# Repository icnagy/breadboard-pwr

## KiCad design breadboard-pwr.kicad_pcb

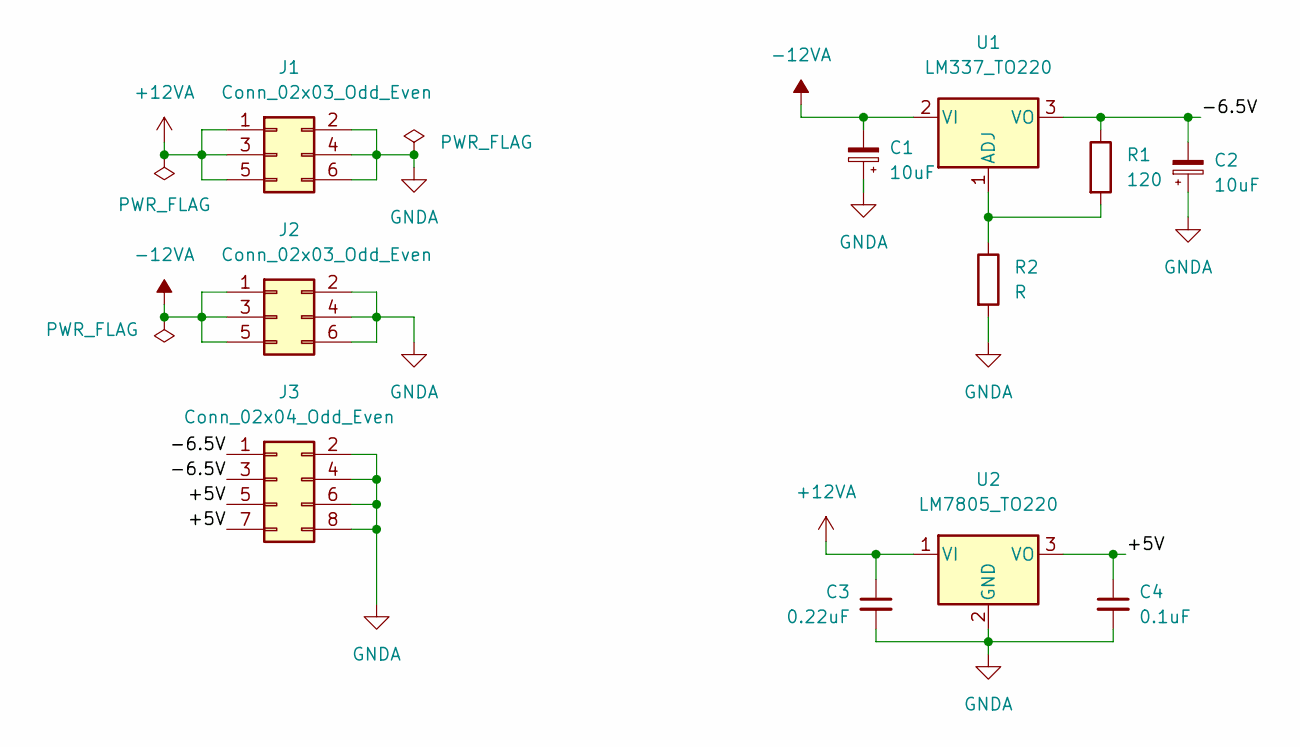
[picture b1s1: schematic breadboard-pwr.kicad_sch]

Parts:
C1, C2: 10uF; CP_Radial_D5.0mm_P2.00mm
C3: 0.22uF; C_Disc_D4.7mm_W2.5mm_P5.00mm
C4: 0.1uF; C_Disc_D4.7mm_W2.5mm_P5.00mm
J1, J2: Conn_02x03_Odd_Even; PinHeader_2x03_P2.54mm_Vertical
J3: Conn_02x04_Odd_Even; PinHeader_2x04_P2.54mm_Vertical
R1: 120; R_Axial_DIN0204_L3.6mm_D1.6mm_P2.54mm_Vertical
R2: R; R_Axial_DIN0204_L3.6mm_D1.6mm_P2.54mm_Vertical
U1: LM337_TO220; TO-220-3_Vertical
U2: LM7805_TO220; TO-220-3_Vertical

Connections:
+12VA: C3.1, J1.1, J1.3, J1.5, U2.1 (VI)
-12VA: C1.2, J2.1, J2.3, J2.5, U1.2 (VI)
/+5V: C4.1, J3.5, J3.7, U2.3 (VO)
/-6.5V: C2.2, J3.1, J3.3, R1.1, U1.3 (VO)
GNDA: C1.1, C2.1, C3.2, C4.2, J1.2, J1.4, J1.6, J2.2, J2.4, J2.6, J3.2, J3.4, J3.6, J3.8, R2.2, U2.2 (GND)
unnamed: R1.2, R2.1, U1.1 (ADJ)

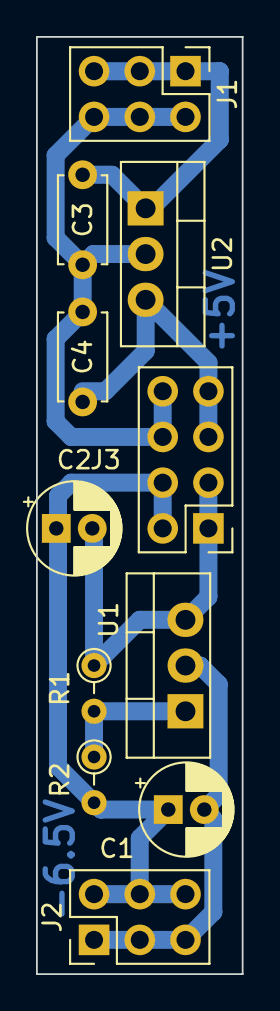
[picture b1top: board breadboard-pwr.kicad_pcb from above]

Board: 2 copper layers, 11.4 x 52.1 mm, 11 parts (0 on the bottom side), 6 nets.

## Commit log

2022-06-10 Add image and schematic
2022-06-10 Add readme
2023-05-29 Kicad 7.0.5 upgrade
